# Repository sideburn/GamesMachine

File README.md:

# Games Machine

KiCad recreation of **"Games Machine — a programmed random number generator"** by D. Burn,
*Practical Electronics*, December 1976 (pp. 969–975). PCB by Sideburn Studios.

A TTL-logic random number generator with four selectable modes:

| Mode | Range | Zero behaviour |
|---|---|---|
| Random | 0–99 | `00` allowed |
| Roulette | 0–36 | `00` allowed |
| Pools | 1–59 | single zero allowed, `00` blocked |
| Dice | 1–6 per digit | no zero in either digit |

Randomness comes from an avalanche-noise transistor (TR1) feeding a two-stage amplifier
(TR2, TR3), squared by a 7413 Schmitt trigger, and gated into a pair of 7490 decade counters
while a 2N2646 UJT relaxation oscillator (TR4) free-runs at 3–4 s. Because the operator's
press and the oscillator phase are uncorrelated, the stopping point is unpredictable. Game
ranges and the zero-detector restart logic come from a diode-resistor matrix (D5–D20) read
through an interlocked pushbutton bank (S1, S3–S6).

## Status

**Rev 1.0** — fabricated 2026-07-09, built and fully bench-tested. All four game modes verified
working against the behaviour described in the original article. Three defects were found and
worked around on the physical board (see below).

**Rev 2.0** — all fixes applied to the KiCad source, DRC clean (0 violations, 0 unconnected),
gerbers and drill files regenerated. Ready to order; not yet fabricated.

### Fixes applied for rev 2.0

| # | Issue | Resolution |
|---|---|---|
| 1 | `LOGIC_0` was a floating net, never tied to ground — board freezes at `99` | Merged into `GND` |
| 2 | Diode silkscreen band marked the anode, so all 17 diodes fitted backwards to the print | Symbol pin numbers swapped, diodes rotated 180° |
| 3 | UNITS/TENS displays placed in reverse reading order — digits read transposed | Placements exchanged |
| 4 | 2N2926 symbol declared E-B-C; the real part is E-C-B, so TR1–TR3 needed crossed leads | Pin numbers corrected |
| 5 | TR4 (2N2646) footprint mapping suspected wrong | Verified correct as drawn — no change |

Full detail, including what was deliberately left alone, is in `Docs/Rev2_Board_Fixes.md`.

## Notes for anyone building one

- **Identify a UJT's leads by measurement, never from a pinout diagram.** Ohms-mode resistive
  pair = the two bases, the leftover lead = emitter; the can-to-lead short then separates B1
  from B2. Two of the three 2N2646s sourced for this build were counterfeit or dead, and one
  passed a static meter test while being unable to fire under real operating bias.
- TR4 wants rotating roughly 10° clockwise of the silkscreen tab mark when fitting — the TO-18
  leads sit on a circle and don't land dead-on the pad angles.

## Repository contents

- `GamesMachine.kicad_sch` / `.kicad_pcb` / `.kicad_pro` — the KiCad project
- `GamesMachine.kicad_sym` — project-local symbol library (custom parts)
- `GamesMachine.stl` — 3D case/board model
- `Gerbers/` — fabrication output, regenerated for rev 2.0
- `Docs/PartsList.md` — full parts list with sourcing notes
- `Docs/BOM.csv` — machine-readable BOM exported from the schematic
- `Docs/BringUp_TestPlan.md` — staged bring-up and test procedure
- `Docs/GameMode_Jumper_Reference.md` — switch/jumper configuration per game mode
- `Docs/Rev2_Board_Fixes.md` — defect record and how each was resolved

The first commit is the rev 1.0 project exactly as fabricated, so the whole set of fixes can be
read as a diff against the board that was actually built.

## Original source

*Practical Electronics*, Vol. 12 No. 12, December 1976. Article by D. Burn, PhD.
The magazine scan is not redistributed here.

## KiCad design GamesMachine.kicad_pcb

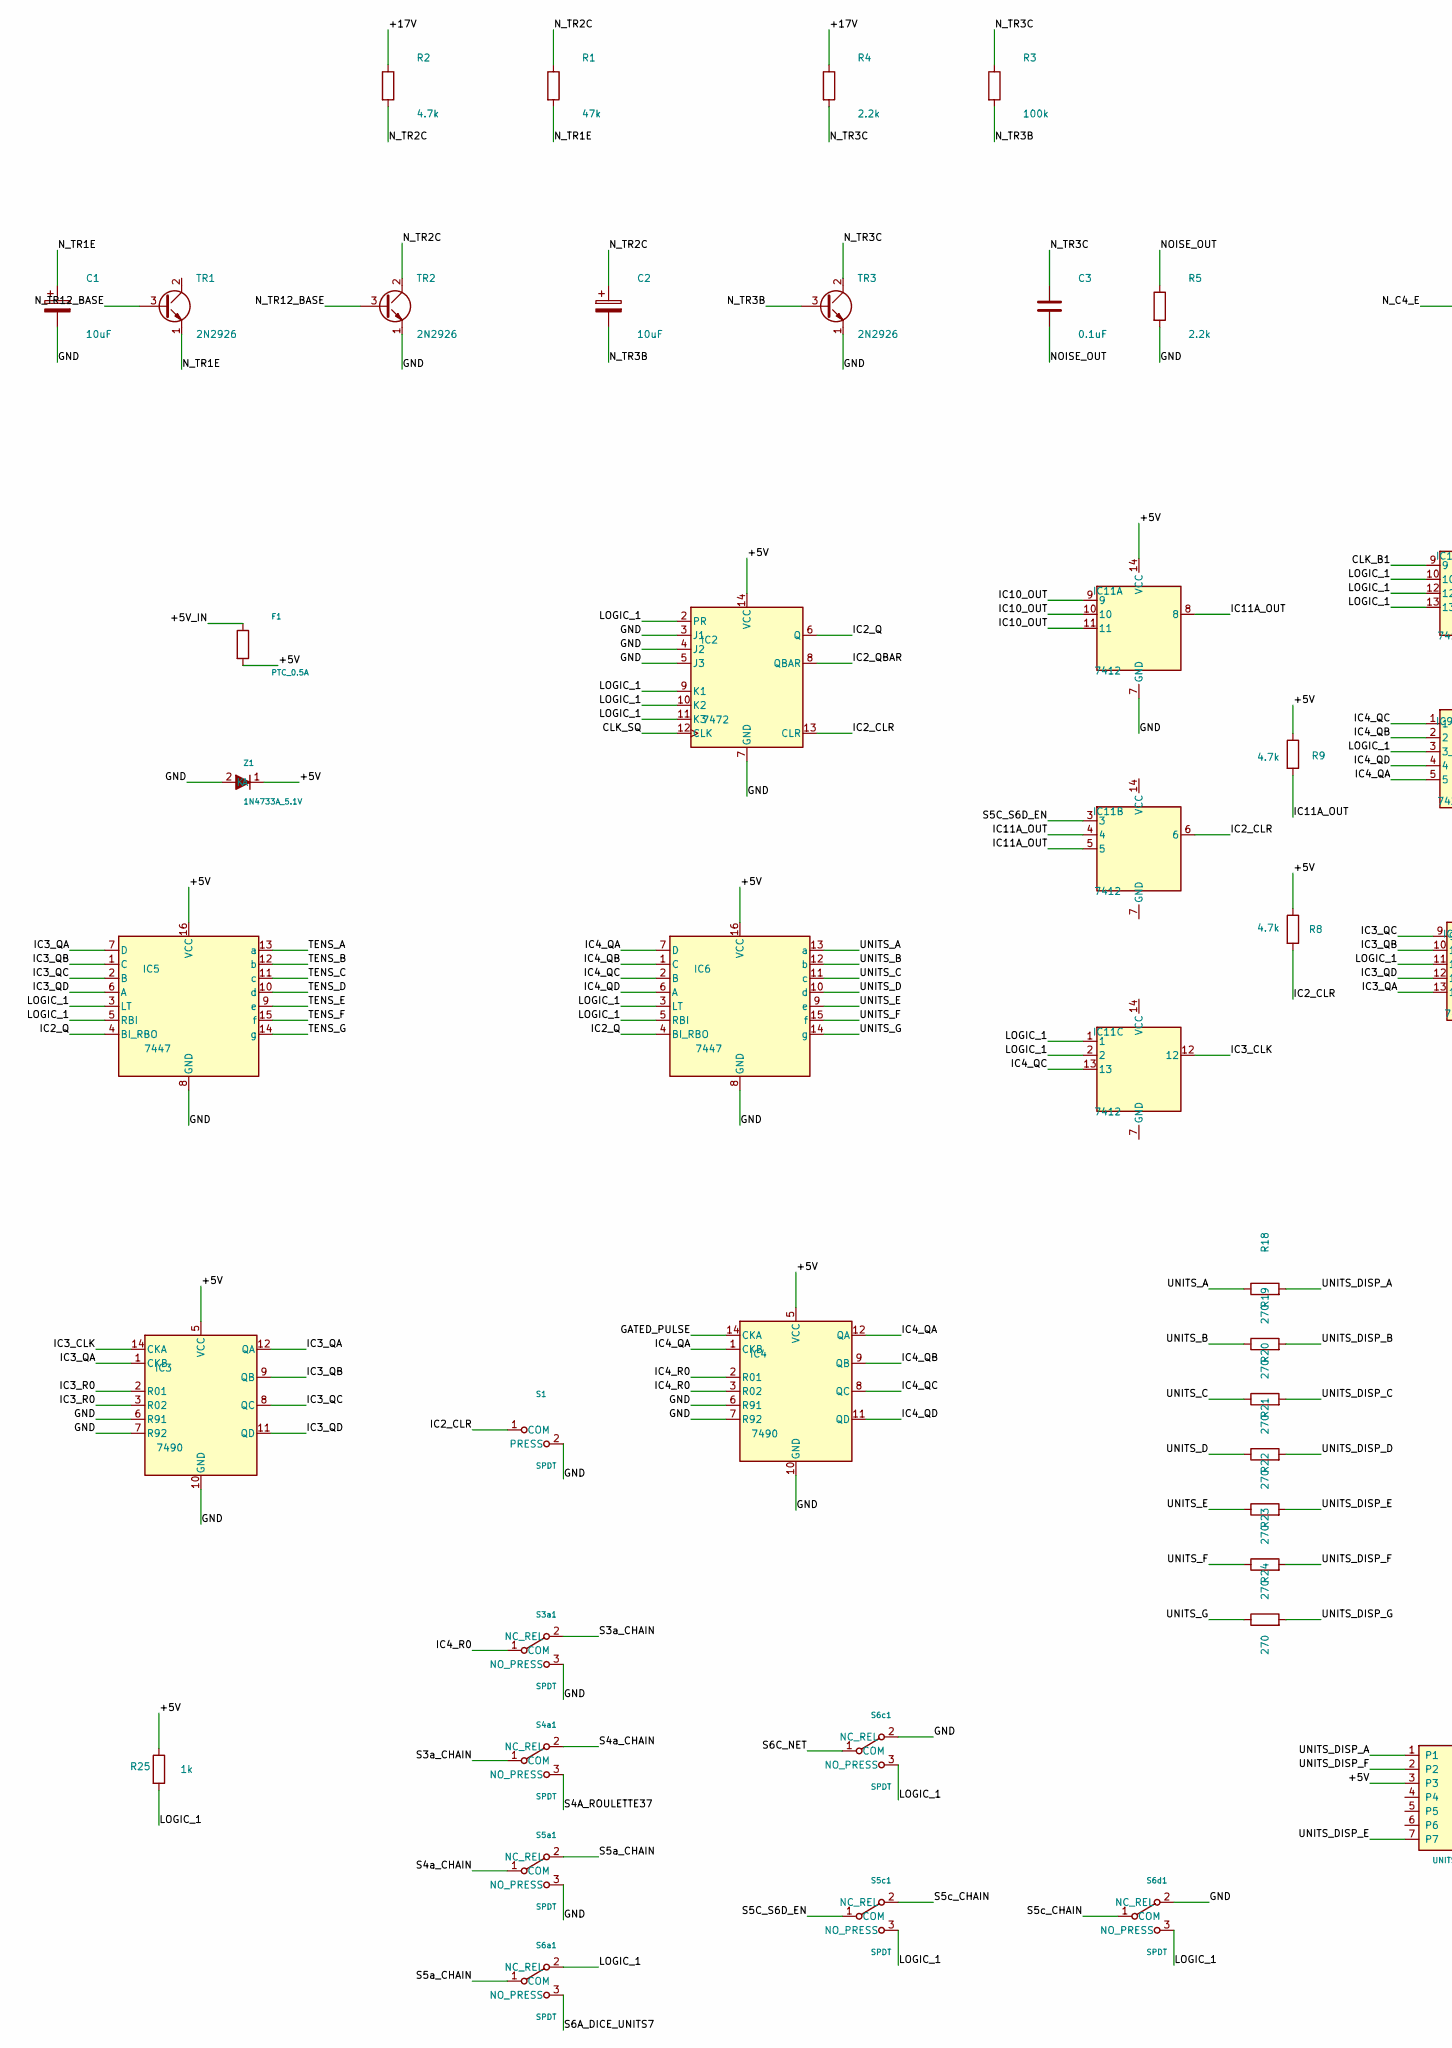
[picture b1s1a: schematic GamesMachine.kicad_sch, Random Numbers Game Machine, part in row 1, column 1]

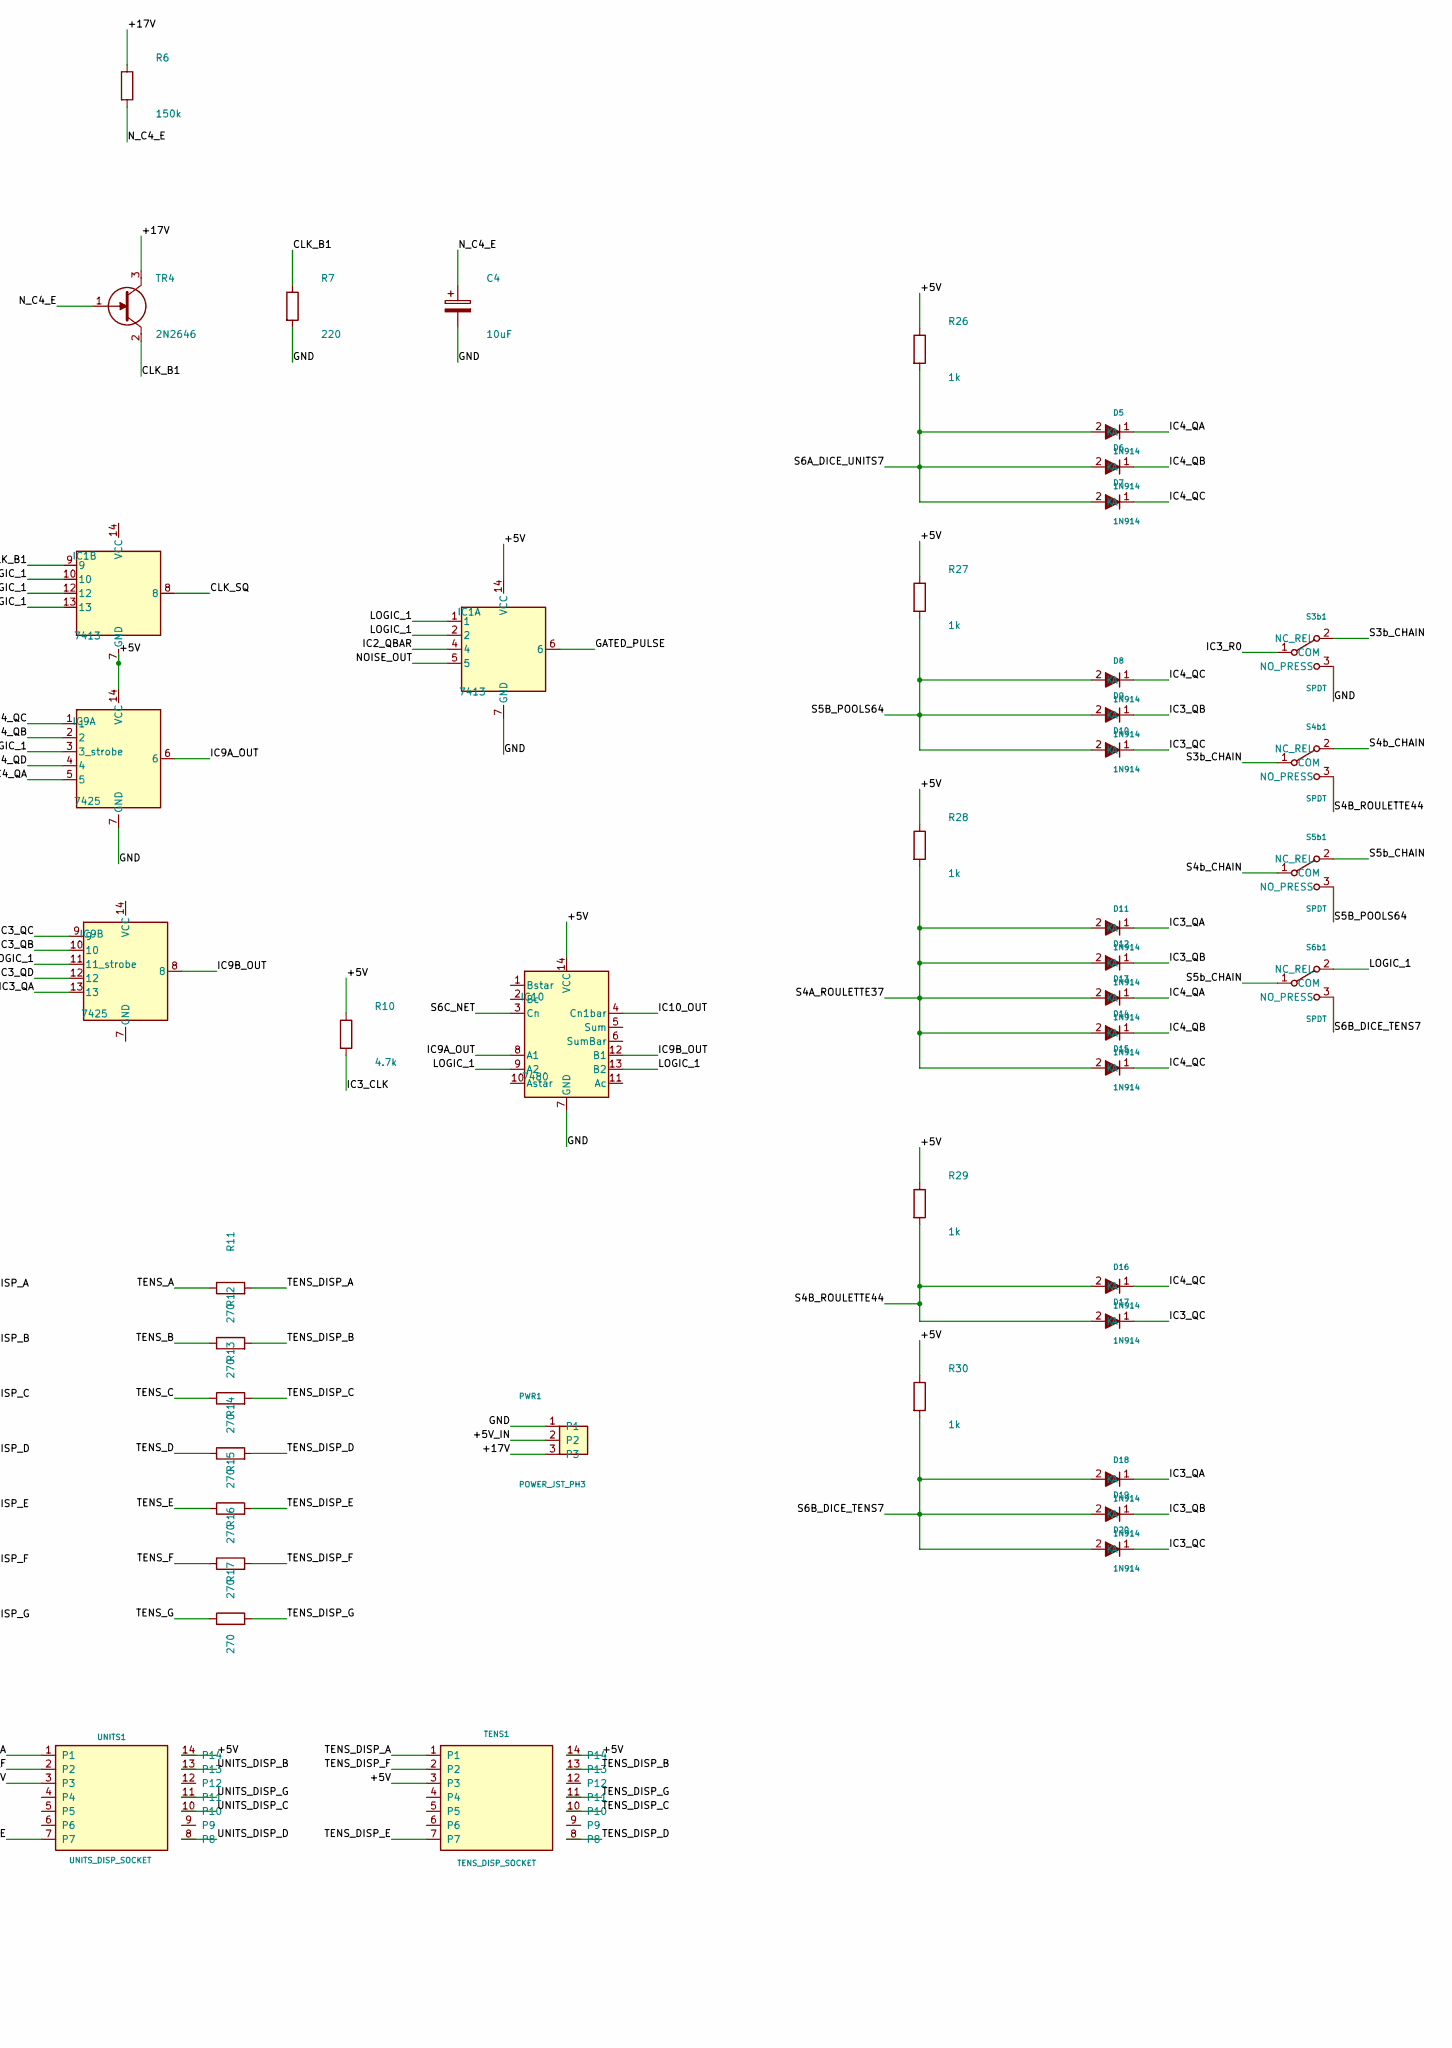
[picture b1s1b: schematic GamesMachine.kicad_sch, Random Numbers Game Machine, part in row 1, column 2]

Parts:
C1, C2, C4: 10uF; CP_Radial_D5.0mm_P2.50mm
C3: 0.1uF; C_Disc_D5.0mm_W2.5mm_P2.50mm
D5, D6, D7, D8, D9, D10, D11, D12, D13, D14, D15, D16, D17, D18, D19, D20: 1N914; D_DO-35_SOD27_P7.62mm_Horizontal
F1: PTC_0.5A; C_Disc_D5.0mm_W2.5mm_P5.00mm
IC1: 7413; DIP-14_W7.62mm
IC2: 7472; DIP-14_W7.62mm
IC3, IC4: 7490; DIP-14_W7.62mm
IC5, IC6: 7447; DIP-16_W7.62mm
IC9: 7425; DIP-14_W7.62mm
IC10: 7480; DIP-14_W7.62mm
IC11: 7412; DIP-14_W7.62mm
PWR1: POWER_JST_PH3; JST_PH_B3B-PH-K_1x03_P2.00mm_Vertical
R1: 47k; R_Axial_DIN0207_L6.3mm_D2.5mm_P10.16mm_Horizontal
R2, R8, R9, R10: 4.7k; R_Axial_DIN0207_L6.3mm_D2.5mm_P10.16mm_Horizontal
R3: 100k; R_Axial_DIN0207_L6.3mm_D2.5mm_P10.16mm_Horizontal
R4, R5: 2.2k; R_Axial_DIN0207_L6.3mm_D2.5mm_P10.16mm_Horizontal
R6: 150k; R_Axial_DIN0207_L6.3mm_D2.5mm_P10.16mm_Horizontal
R7: 220; R_Axial_DIN0207_L6.3mm_D2.5mm_P10.16mm_Horizontal
R11, R12, R13, R14, R15, R16, R17, R18, R19, R20, R21, R22, R23, R24: 270; R_Axial_DIN0207_L6.3mm_D2.5mm_P10.16mm_Horizontal
R25, R26, R27, R28, R29, R30: 1k; R_Axial_DIN0207_L6.3mm_D2.5mm_P10.16mm_Horizontal
S1: SPDT; JST_PH_B2B-PH-K_1x02_P2.00mm_Vertical
S3a1, S3b1, S4a1, S4b1, S5a1, S5b1, S5c1, S6a1, S6b1, S6c1, S6d1: SPDT; JST_PH_B3B-PH-K_1x03_P2.00mm_Vertical
TENS1: TENS_DISP_SOCKET; DIP-14_W7.62mm
TR1, TR2, TR3: 2N2926; TO-92_Inline
TR4: 2N2646; TO-18-3
UNITS1: UNITS_DISP_SOCKET; DIP-14_W7.62mm
Z1: 1N4733A_5.1V; D_DO-41_SOD81_P10.16mm_Horizontal

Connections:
/+5V_IN: F1.1, PWR1.2
/+17V: PWR1.3, R2.1, R4.1, R6.1, TR4.3 (B2)
/CLK_B1: IC1.9, R7.1, TR4.2 (B1)
/CLK_SQ: IC1.8, IC2.12 (CLK)
/GATED_PULSE: IC1.6, IC4.14 (CKA)
/IC2_CLR: IC2.13 (CLR), IC11.6, R8.2, S1.1 (COM)
/IC2_Q: IC2.6 (Q), IC5.4 (BI_RBO), IC6.4 (BI_RBO)
/IC2_QBAR: IC1.4, IC2.8 (QBAR)
/IC3_CLK: IC3.14 (CKA), IC11.12, R10.2
/IC3_QA: D11.1 (K), D18.1 (K), IC3.1 (CKB), IC3.12 (QA), IC5.7 (D), IC9.13
/IC3_QB: D9.1 (K), D12.1 (K), D19.1 (K), IC3.9 (QB), IC5.1 (C), IC9.10
/IC3_QC: D10.1 (K), D17.1 (K), D20.1 (K), IC3.8 (QC), IC5.2 (B), IC9.9
/IC3_QD: IC3.11 (QD), IC5.6 (A), IC9.12
/IC3_R0: IC3.2 (R01), IC3.3 (R02), S3b1.1 (COM)
/IC4_QA: D5.1 (K), D13.1 (K), IC4.1 (CKB), IC4.12 (QA), IC6.7 (D), IC9.5
/IC4_QB: D6.1 (K), D14.1 (K), IC4.9 (QB), IC6.1 (C), IC9.2
/IC4_QC: D7.1 (K), D8.1 (K), D15.1 (K), D16.1 (K), IC4.8 (QC), IC6.2 (B), IC9.1, IC11.13
/IC4_QD: IC4.11 (QD), IC6.6 (A), IC9.4
/IC4_R0: IC4.2 (R01), IC4.3 (R02), S3a1.1 (COM)
/IC9A_OUT: IC9.6, IC10.8 (A1)
/IC9B_OUT: IC9.8, IC10.12 (B1)
/IC10_OUT: IC10.4 (Cn1bar), IC11.9, IC11.10, IC11.11
/IC11A_OUT: IC11.4, IC11.5, IC11.8, R9.2
/LOGIC_1: IC1.1, IC1.2, IC1.10, IC1.12, IC1.13, IC2.2 (PR), IC2.9 (K1), IC2.10 (K2), IC2.11 (K3), IC5.3 (LT), IC5.5 (RBI), IC6.3 (LT), IC6.5 (RBI), IC9.3 (3_strobe), IC9.11 (11_strobe), IC10.9 (A2), IC10.13 (B2), IC11.1, IC11.2, R25.2, S5c1.3 (NO_PRESS), S6a1.2 (NC_REL), S6b1.2 (NC_REL), S6c1.3 (NO_PRESS), S6d1.3 (NO_PRESS)
/NOISE_OUT: C3.2, IC1.5, R5.1
/N_C4_E: C4.1, R6.2, TR4.1 (E)
/N_TR1E: C1.1, R1.2, TR1.1 (E)
/N_TR2C: C2.1, R1.1, R2.2, TR2.2 (C)
/N_TR3B: C2.2, R3.2, TR3.3 (B)
/N_TR3C: C3.1, R3.1, R4.2, TR3.2 (C)
/N_TR12_BASE: TR1.3 (B), TR2.3 (B)
/S3a_CHAIN: S3a1.2 (NC_REL), S4a1.1 (COM)
/S3b_CHAIN: S3b1.2 (NC_REL), S4b1.1 (COM)
/S4A_ROULETTE37: D11.2 (A), D12.2 (A), D13.2 (A), D14.2 (A), D15.2 (A), R28.2, S4a1.3 (NO_PRESS)
/S4B_ROULETTE44: D16.2 (A), D17.2 (A), R29.2, S4b1.3 (NO_PRESS)
/S4a_CHAIN: S4a1.2 (NC_REL), S5a1.1 (COM)
/S4b_CHAIN: S4b1.2 (NC_REL), S5b1.1 (COM)
/S5B_POOLS64: D8.2 (A), D9.2 (A), D10.2 (A), R27.2, S5b1.3 (NO_PRESS)
/S5C_S6D_EN: IC11.3, S5c1.1 (COM)
/S5a_CHAIN: S5a1.2 (NC_REL), S6a1.1 (COM)
/S5b_CHAIN: S5b1.2 (NC_REL), S6b1.1 (COM)
/S5c_CHAIN: S5c1.2 (NC_REL), S6d1.1 (COM)
/S6A_DICE_UNITS7: D5.2 (A), D6.2 (A), D7.2 (A), R26.2, S6a1.3 (NO_PRESS)
/S6B_DICE_TENS7: D18.2 (A), D19.2 (A), D20.2 (A), R30.2, S6b1.3 (NO_PRESS)
/S6C_NET: IC10.3 (Cn), S6c1.1 (COM)
/TENS_A: IC5.13 (a), R11.1
/TENS_B: IC5.12 (b), R12.1
/TENS_C: IC5.11 (c), R13.1
/TENS_D: IC5.10 (d), R14.1
/TENS_DISP_A: R11.2, TENS1.1
/TENS_DISP_B: R12.2, TENS1.13
/TENS_DISP_C: R13.2, TENS1.10
/TENS_DISP_D: R14.2, TENS1.8
/TENS_DISP_E: R15.2, TENS1.7
/TENS_DISP_F: R16.2, TENS1.2
/TENS_DISP_G: R17.2, TENS1.11
/TENS_E: IC5.9 (e), R15.1
/TENS_F: IC5.15 (f), R16.1
/TENS_G: IC5.14 (g), R17.1
/UNITS_A: IC6.13 (a), R18.1
/UNITS_B: IC6.12 (b), R19.1
/UNITS_C: IC6.11 (c), R20.1
/UNITS_D: IC6.10 (d), R21.1
/UNITS_DISP_A: R18.2, UNITS1.1
/UNITS_DISP_B: R19.2, UNITS1.13
/UNITS_DISP_C: R20.2, UNITS1.10
/UNITS_DISP_D: R21.2, UNITS1.8
/UNITS_DISP_E: R22.2, UNITS1.7
/UNITS_DISP_F: R23.2, UNITS1.2
/UNITS_DISP_G: R24.2, UNITS1.11
/UNITS_E: IC6.9 (e), R22.1
/UNITS_F: IC6.15 (f), R23.1
/UNITS_G: IC6.14 (g), R24.1

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
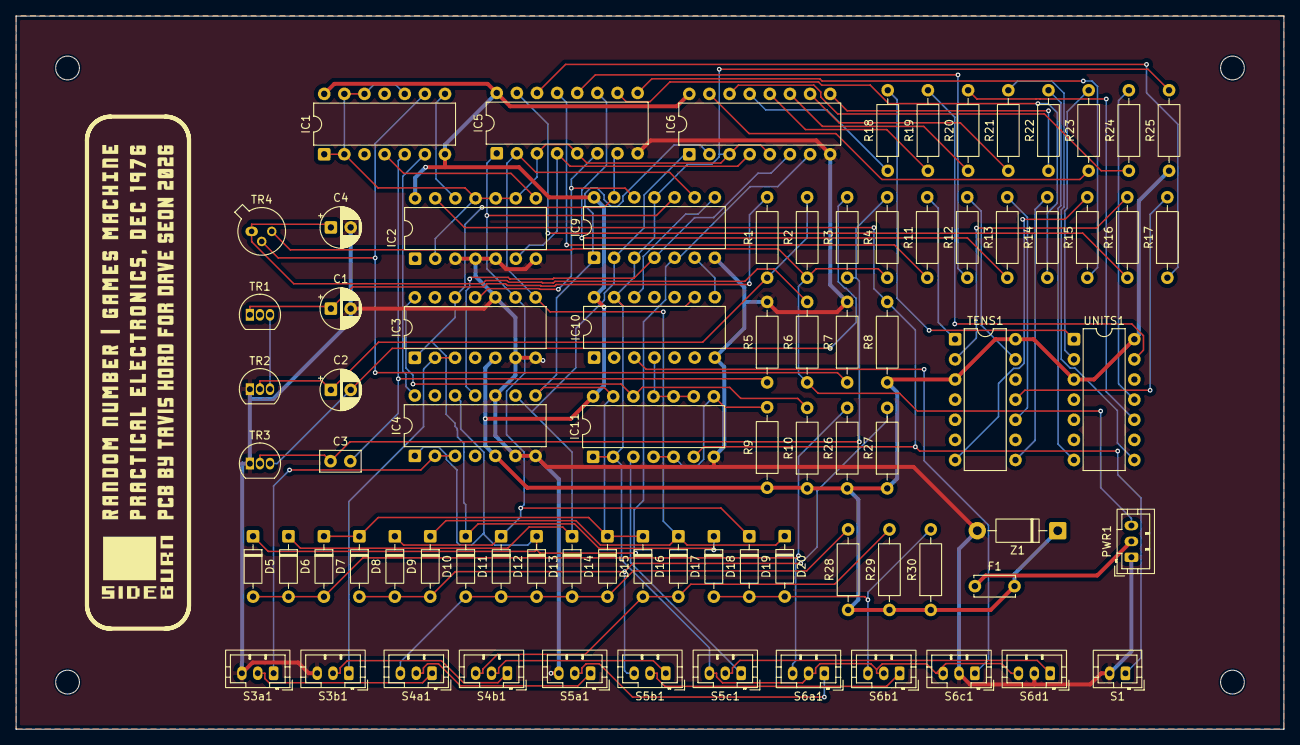
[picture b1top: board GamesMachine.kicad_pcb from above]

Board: 2 copper layers, 160.0 x 90.0 mm, 84 parts (0 on the bottom side), 75 nets.

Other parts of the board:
BLMH: MountingHole_3mm
BRMH: MountingHole_3mm
TLMH: MountingHole_3mm
TRMH: MountingHole_3mm

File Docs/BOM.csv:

"Refs","Value","Footprint","Qty"
"C1,C2,C4","10uF","Capacitor_THT:CP_Radial_D5.0mm_P2.50mm","3"
"C3","0.1uF","Capacitor_THT:C_Disc_D5.0mm_W2.5mm_P2.50mm","1"
"D5-D20","1N914","Diode_THT:D_DO-35_SOD27_P7.62mm_Horizontal","16"
"F1","PTC_0.5A","Capacitor_THT:C_Disc_D5.0mm_W2.5mm_P5.00mm","1"
"IC1","7413","Package_DIP:DIP-14_W7.62mm","1"
"IC2","7472","Package_DIP:DIP-14_W7.62mm","1"
"IC3,IC4","7490","Package_DIP:DIP-14_W7.62mm","2"
"IC5,IC6","7447","Package_DIP:DIP-16_W7.62mm","2"
"IC9","7425","Package_DIP:DIP-14_W7.62mm","1"
"IC10","7480","Package_DIP:DIP-14_W7.62mm","1"
"IC11","7412","Package_DIP:DIP-14_W7.62mm","1"
"PWR1","POWER_JST_PH3","Connector_JST:JST_PH_B3B-PH-K_1x03_P2.00mm_Vertical","1"
"R1","47k","Resistor_THT:R_Axial_DIN0207_L6.3mm_D2.5mm_P10.16mm_Horizontal","1"
"R2,R8-R10","4.7k","Resistor_THT:R_Axial_DIN0207_L6.3mm_D2.5mm_P10.16mm_Horizontal","4"
"R3","100k","Resistor_THT:R_Axial_DIN0207_L6.3mm_D2.5mm_P10.16mm_Horizontal","1"
"R4,R5","2.2k","Resistor_THT:R_Axial_DIN0207_L6.3mm_D2.5mm_P10.16mm_Horizontal","2"
"R6","150k","Resistor_THT:R_Axial_DIN0207_L6.3mm_D2.5mm_P10.16mm_Horizontal","1"
"R7","220","Resistor_THT:R_Axial_DIN0207_L6.3mm_D2.5mm_P10.16mm_Horizontal","1"
"R11-R24","270","Resistor_THT:R_Axial_DIN0207_L6.3mm_D2.5mm_P10.16mm_Horizontal","14"
"R25-R30","1k","Resistor_THT:R_Axial_DIN0207_L6.3mm_D2.5mm_P10.16mm_Horizontal","6"
"S1","SPDT","Connector_JST:JST_PH_B2B-PH-K_1x02_P2.00mm_Vertical","1"
"S3a1,S3b1,S4a1,S4b1,S5a1,S5b1,S5c1,S6a1,S6b1,S6c1,S6d1","SPDT","Connector_JST:JST_PH_B3B-PH-K_1x03_P2.00mm_Vertical","11"
"TENS1","TENS_DISP_SOCKET","Package_DIP:DIP-14_W7.62mm","1"
"TR1-TR3","2N2926","Package_TO_SOT_THT:TO-92_Inline","3"
"TR4","2N2646","Package_TO_SOT_THT:TO-18-3","1"
"UNITS1","UNITS_DISP_SOCKET","Package_DIP:DIP-14_W7.62mm","1"
"Z1","1N4733A_5.1V","Diode_THT:D_DO-41_SOD81_P10.16mm_Horizontal","1"
